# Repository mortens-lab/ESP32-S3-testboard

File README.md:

# ESP32-S3-testboard
KiCad files

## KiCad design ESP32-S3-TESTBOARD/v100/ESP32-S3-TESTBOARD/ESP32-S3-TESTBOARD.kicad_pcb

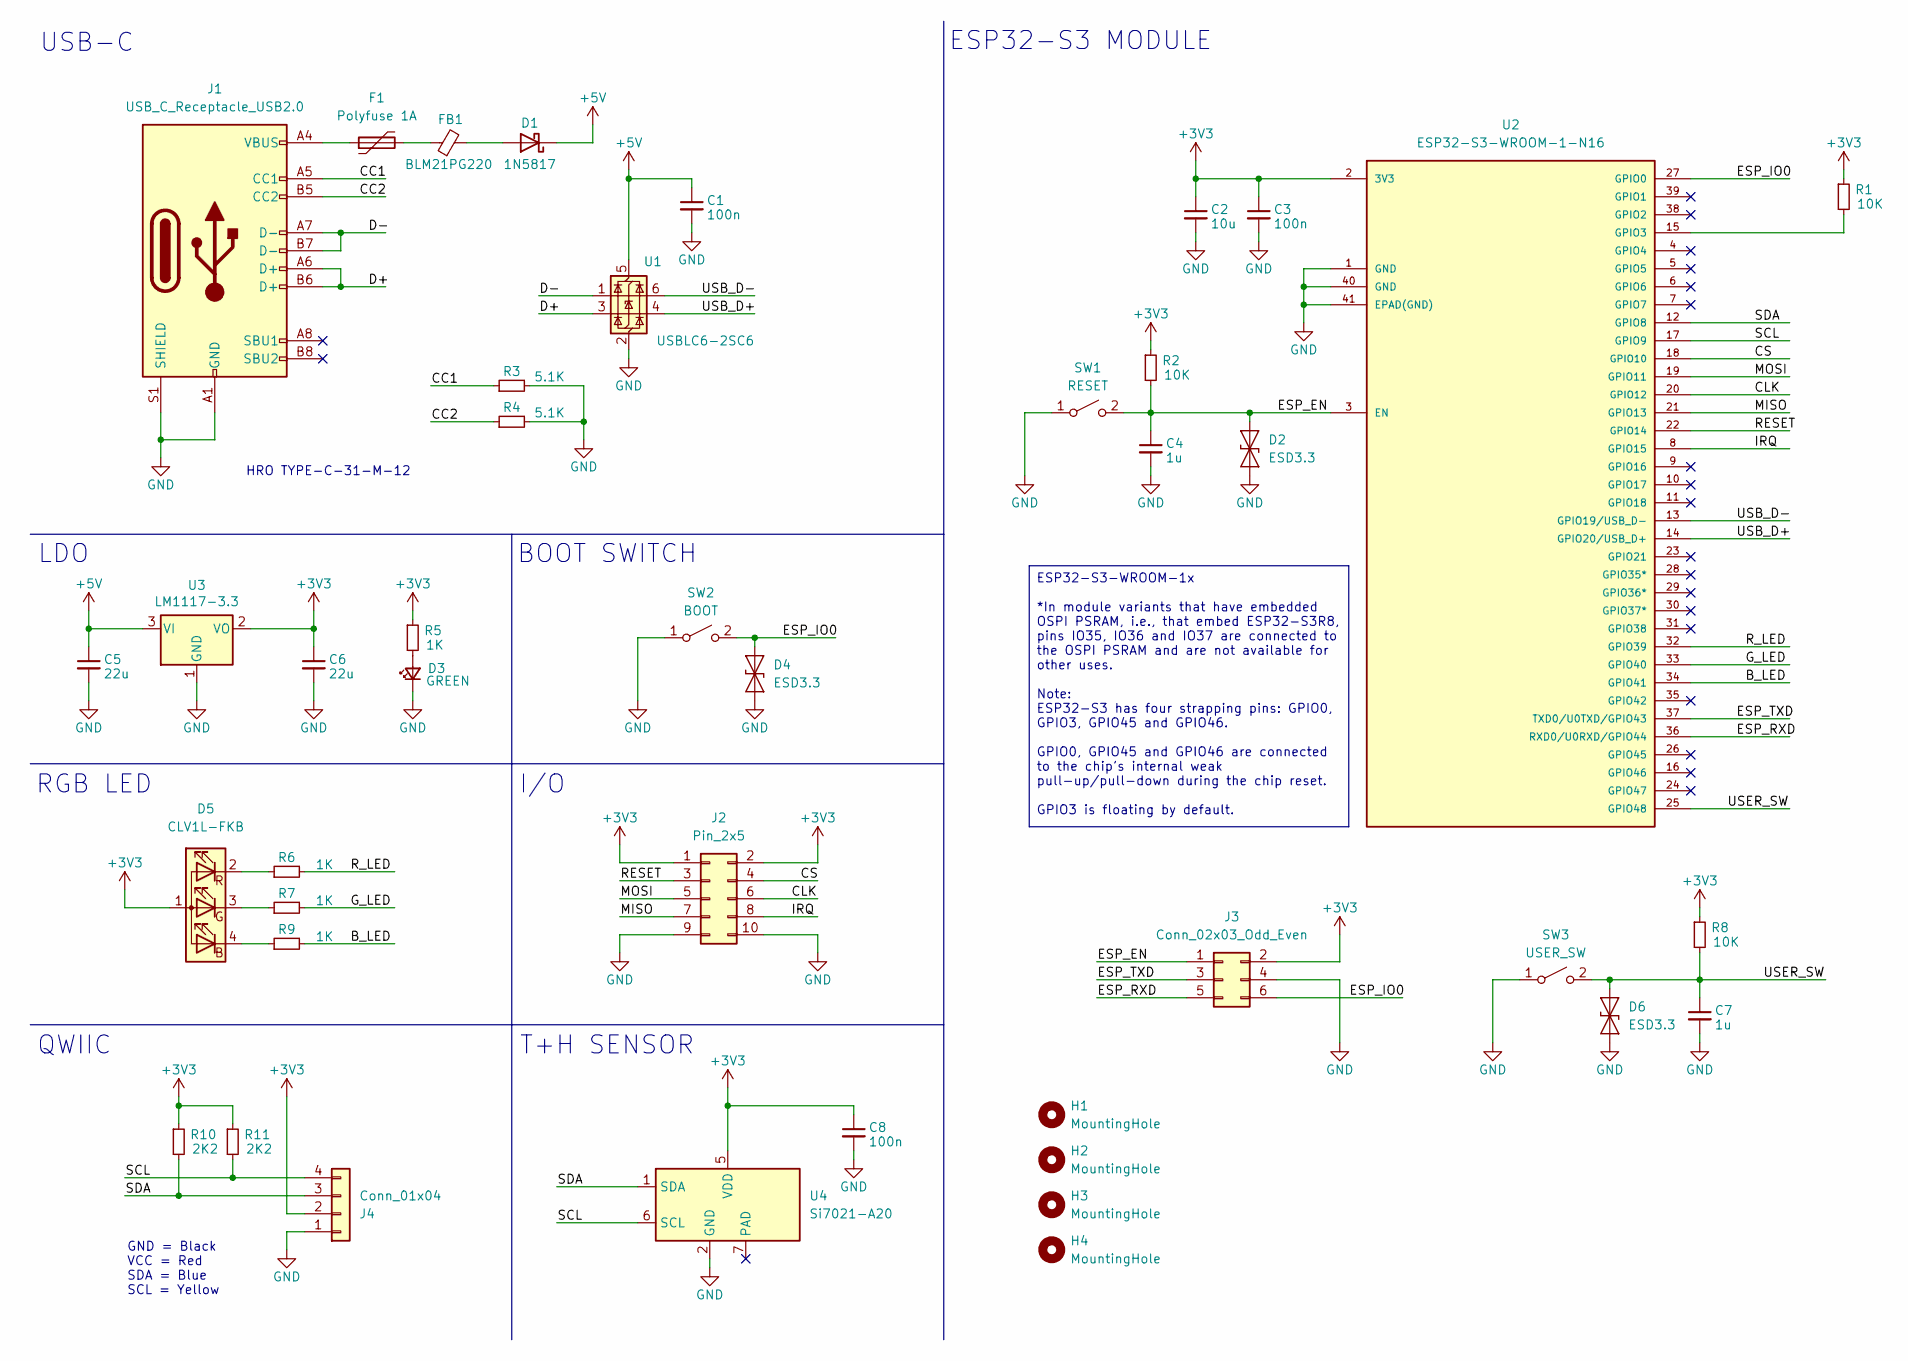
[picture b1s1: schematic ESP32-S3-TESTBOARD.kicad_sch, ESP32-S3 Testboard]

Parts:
C1, C3, C8: 100n; C_0402_1005Metric_Pad0.74x0.62mm_HandSolder
C2: 10u; C_0603_1608Metric
C4, C7: 1u; C_0603_1608Metric
C5, C6: 22u; C_0805_2012Metric
D1: 1N5817; D_SOD-123
D2, D4, D6: ESD3.3; D_SOD-923
D3: GREEN; LED_0603_1608Metric
D5: CLV1L-FKB; LED_Cree-PLCC4_3.2x2.8mm_CCW
F1: Polyfuse 1A; Fuse_1206_3216Metric
FB1: BLM21PG220; L_0805_2012Metric
H1, H2, H3, H4: MountingHole; MountingHole_3.2mm_M3
J1: USB_C_Receptacle_USB2.0; USB_C_Receptacle_HRO_TYPE-C-31-M-12
J2: Pin_2x5; PinHeader_2x05_P2.54mm_Vertical
J3: Conn_02x03_Odd_Even; PinHeader_2x03_P2.54mm_Vertical
J4: Conn_01x04; JST_SH_SM04B-SRSS-TB_1x04-1MP_P1.00mm_Horizontal
R1, R2, R8: 10K; R_0402_1005Metric
R3, R4: 5.1K; R_0402_1005Metric
R5, R6, R7, R9: 1K; R_0402_1005Metric
R10, R11: 2K2; R_0402_1005Metric
SW1: RESET; SW_SPST_B3U-1000P
SW2: BOOT; SW_SPST_B3U-1000P
SW3: USER_SW; SW_Tactile_SPST_Angled_PTS645Vx31-2LFS
U1: USBLC6-2SC6; SOT-23-6
U2: ESP32-S3-WROOM-1-N16; ESP32-S3-WROOM-1
U3: LM1117-3.3; SOT-223-3_TabPin2
U4: Si7021-A20; DFN-6-1EP_3x3mm_P1mm_EP1.5x2.4mm

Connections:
+3V3: C2.1, C3.1, C6.1, C8.1, D5.1 (A), J2.1, J2.2, J3.2, J4.2, R1.1, R2.1, R5.1, R8.1, R10.1, R11.1, U2.2 (3V3), U3.2 (VO), U4.5 (VDD)
+5V: C1.1, C5.1, D1.1 (K), U1.5 (VBUS), U3.3 (VI)
/B_LED: R9.2, U2.34 (GPIO41)
/CC1: J1.A5 (CC1), R3.1
/CC2: J1.B5 (CC2), R4.1
/CLK: J2.6, U2.20 (GPIO12)
/CS: J2.4, U2.18 (GPIO10)
/D+: J1.A6 (D+), J1.B6 (D+), U1.3 (I/O2)
/D-: J1.A7 (D-), J1.B7 (D-), U1.1 (I/O1)
/ESP_EN: C4.1, D2.2 (A2), J3.1, R2.2, SW1.2 (B), U2.3 (EN)
/ESP_IO0: D4.2 (A2), J3.6, SW2.2 (B), U2.27 (GPIO0)
/ESP_RXD: J3.5, U2.36 (RXD0/U0RXD/GPIO44)
/ESP_TXD: J3.3, U2.37 (TXD0/U0TXD/GPIO43)
/G_LED: R7.2, U2.33 (GPIO40)
/IRQ: J2.8, U2.8 (GPIO15)
/MISO: J2.7, U2.21 (GPIO13)
/MOSI: J2.5, U2.19 (GPIO11)
/RESET: J2.3, U2.22 (GPIO14)
/R_LED: R6.2, U2.32 (GPIO39)
/SCL: J4.4, R11.2, U2.17 (GPIO9), U4.6 (SCL)
/SDA: J4.3, R10.2, U2.12 (GPIO8), U4.1 (SDA)
/USB_D+: U1.4 (I/O2), U2.14 (GPIO20/USB_D+)
/USB_D-: U1.6 (I/O1), U2.13 (GPIO19/USB_D-)
/USER_SW: C7.1, D6.2 (A2), R8.2, SW3.2 (B), U2.25 (GPIO48)
GND: C1.2, C2.2, C3.2, C4.2, C5.2, C6.2, C7.2, C8.2, D2.1 (A1), D3.1 (K), D4.1 (A1), D6.1 (A1), J1.A1 (GND), J1.A12 (GND), J1.B1 (GND), J1.B12 (GND), J1.S1 (SHIELD), J2.9, J2.10, J3.4, J4.1, R3.2, R4.2, SW1.1 (A), SW2.1 (A), SW3.1 (A), U1.2 (GND), U2.1 (GND), U2.40 (GND), U2.41 (EPAD(GND)), U3.1 (GND), U4.2 (GND)
unnamed: D1.2 (A), FB1.2
unnamed: D3.2 (A), R5.2
unnamed: D5.4 (BK), R9.1
unnamed: D5.3 (GK), R7.1
unnamed: D5.2 (RK), R6.1
unnamed: F1.1, J1.A4 (VBUS), J1.A9 (VBUS), J1.B4 (VBUS), J1.B9 (VBUS)
unnamed: F1.2, FB1.1
unnamed: R1.2, U2.15 (GPIO3)

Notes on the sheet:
LDO
USB-C
T+H SENSOR
RGB LED
QWIIC
I/O
BOOT SWITCH
HRO TYPE-C-31-M-12
GND = Black VCC = Red SDA = Blue SCL = Yellow
ESP32-S3 MODULE
ESP32-S3-WROOM-1x *In module variants that have embedded OSPI PSRAM, i.e., that embed ESP32-S3R8, pins IO35, IO36 and IO37 are connected to the OSPI PSRAM and are not available for other uses. Note: ESP32-S3 has four strapping pins: GPIO0, GPIO3, GPIO45 and GPIO46. GPIO0, GPIO45 and GPIO46 are conn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

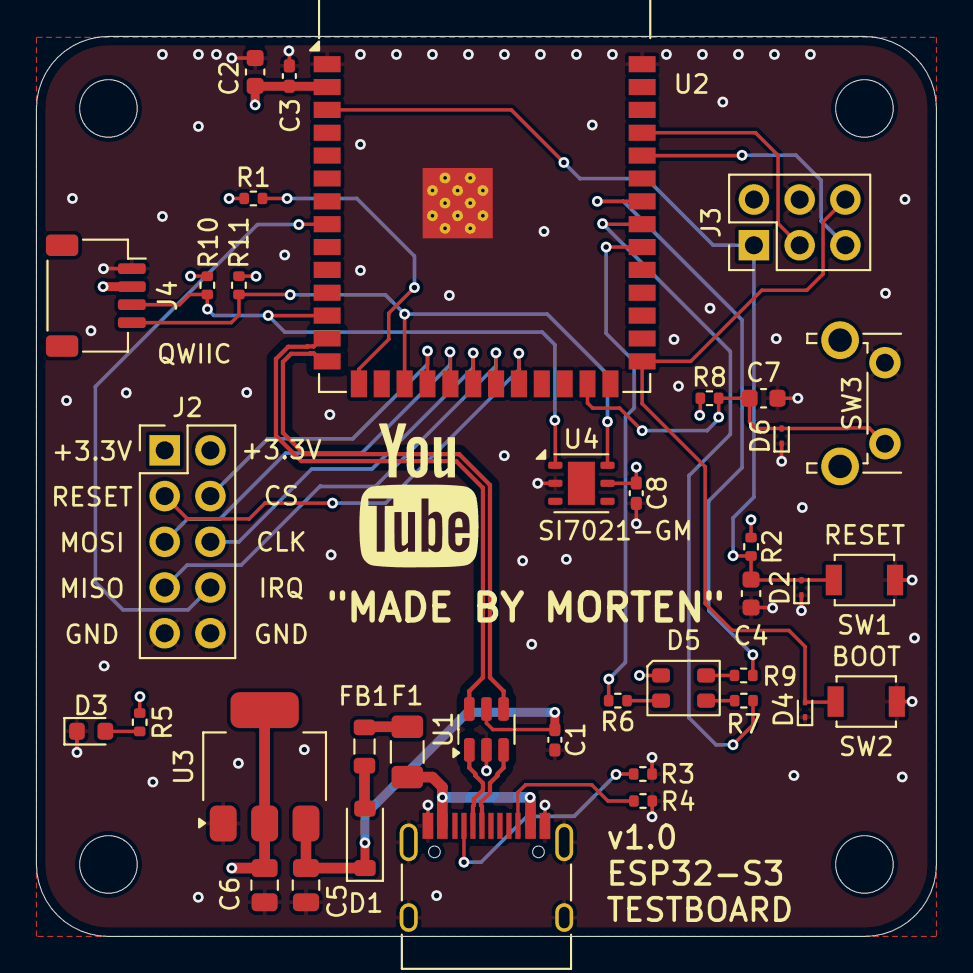
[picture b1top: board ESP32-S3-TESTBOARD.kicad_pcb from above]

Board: 4 copper layers, 50.0 x 50.0 mm, 42 parts (0 on the bottom side), 33 nets.
